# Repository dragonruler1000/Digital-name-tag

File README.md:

# Primortia nametag
i made this sense i wanted a way to have a name tag that had more personality then just a basic printed name tag. sense i have already designed a rp2040 devboard i decided to use that as the MCU. this has a pretty simple design so tobmake it your self you just need to get the pcb made then get all the other parts. sense one of the pins that is being used for the adc functionality in in a place that usually wouldn't have it printing my custom devboard is recommended unless you want to change the symbol to a regular pico.

BOM:
| Item Count | item name       | Unit price $ | Total Price* | Price with discounts* | Link                                                                                                               | Running total $* | Running total with coupons*    | part number | Notes                                   |
|------------|-----------------|--------------|--------------|-----------------------|--------------------------------------------------------------------------------------------------------------------|------------------|--------------------------------|-------------|-----------------------------------------|
| 1          | Blue LED        | 0.19         | 0.19         | 0.19                  | https://www.digikey.com/en/products/detail/american-bright-optoelectronics-corporation/BL-BBX1V4V-2-B02/22486905   | 0.2              | 0.2                            | 1           |                                         |
| 0          | Red LED         | 0            | 0            | 0                     | https://www.lcsc.com/product-detail/C99771.html                                                                    | 0.2              | 0.2                            | 2           | have some left over from a past project |
| 0          | Green LED       | 0            | 0            | 0                     | https://www.jameco.com/z/MCDL-5013GD-MCD-Electronics-LED-Green-Diffused-5mm-T-1-3-4-565nm-12-5mcd-60VA_693901.html | 0.2              | 0.2                            | 3           | have some left over from a past project |
| 1          | 5.1Ω resistor   | 0.1          | 0.1          | 0.1                   | https://www.digikey.com/en/products/detail/yageo/CFR-25JB-52-5R1/2238                                              | 0.31             | 0.31                           | 4           |                                         |
| 1          | 56Ω resistor    | 0.1          | 0.1          | 0.1                   | https://www.digikey.com/en/products/detail/te-connectivity-passive-product/LR1F56R/2381266                         | 0.42             | 0.42                           | 5           |                                         |
| 1          | 120Ω resistor   | 0.1          | 0.1          | 0.1                   | https://www.digikey.com/en/products/detail/ohmite/OK1215E-R52/5972032                                              | 0.53             | 0.53                           | 6           |                                         |
| 1          | 100kΩ resistor  | 0.1          | 0.1          | 0.1                   | https://www.digikey.com/en/products/detail/te-connectivity-passive-product/LR1F100K/2381157                        | 0.64             | 0.64                           | 7           |                                         |
| 1          | 68kΩ resistor   | 0.1          | 0.1          | 0.1                   | https://www.digikey.com/en/products/detail/yageo/MFR50SFTE52-68K/9151668                                           | 0.75             | 0.75                           | 8           |                                         |
| 1          | buzzer          | 0.76         | 0.76         | 0.76                  | https://www.digikey.com/en/products/detail/ole-wolff-electronics-inc/OWPB-1360P3-5-40-03/27621007                  | 1.56             | 1.56                           | 9           |                                         |
| 3          | buttons         | 0.13         | 0.39         | 0.39                  | https://www.digikey.com/en/products/detail/te-connectivity-alcoswitch-switches/1825910-6/1632536                   | 1.97             | 1.97                           | 10          | have one left over from a past project  |
| 1          | battery holder  | 2.29         | 2.29         | 2.29                  | https://www.digikey.com/en/products/detail/keystone-electronics/2479RB/2746483                                     | 4.4              | 4.4                            | 11          |                                         |
| 1          | 0.91” oled      | 5.02         | 5.02         | 5.02                  | https://www.lcsc.com/product-detail/C5248081.html                                                                  | 9.72             | 9.72                           | 12          |                                         |
| 1          | PCB             | 5.3          | 5.3          | 5.3                   | https://jlcpcb.com                                                                                                 | 15.34            | 15.34                          | 13          |                                         |
| 1          | JLCPCB shipping | 3.3          | 3.3          | 3.3                   |                                                                                                                    | 18.84            | 18.84                          | 14          |                                         |
| 1          | digikeyshipping | 6.99         | 6.99         | 6.99                  |                                                                                                                    | 26.25            | 26.25                          | 15          |                                         |
|            |                 |              |              |                       |                                                                                                                    |                  | *Rounded to two decimal places |             |                                         |

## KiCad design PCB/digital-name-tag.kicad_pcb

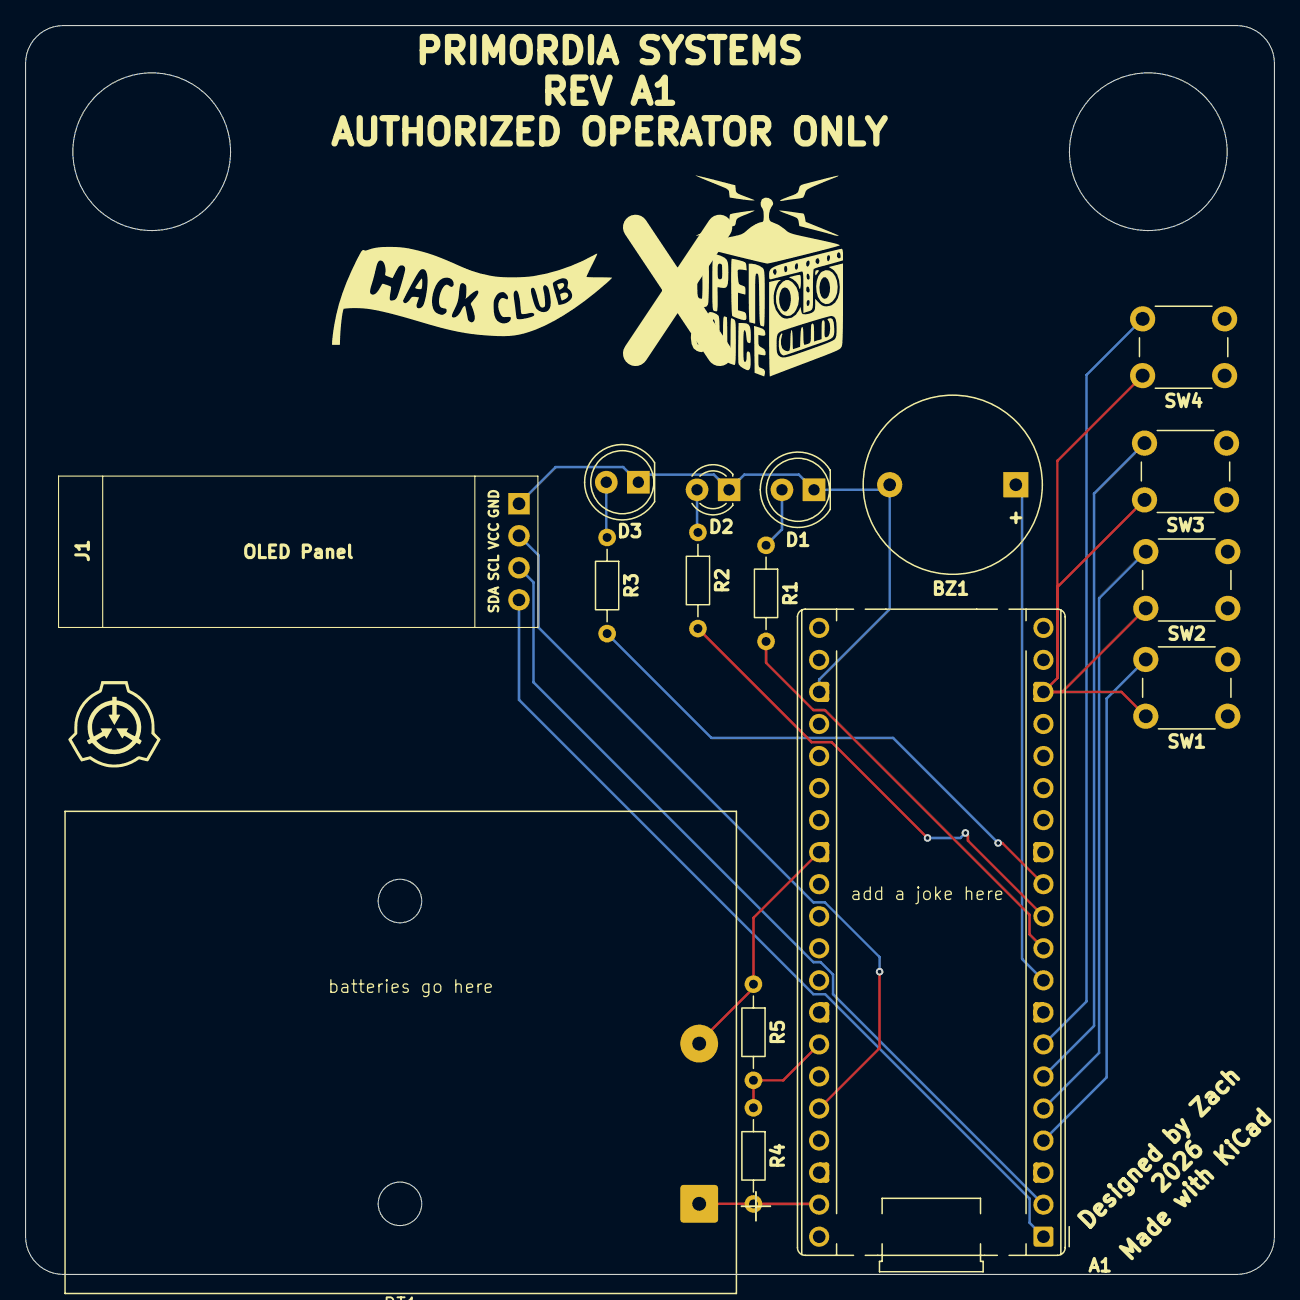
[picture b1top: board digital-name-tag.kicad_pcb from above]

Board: 2 copper layers, 99.0 x 99.0 mm, 16 parts (0 on the bottom side), 17 nets.

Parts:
A1: Primordia_Devboard; RaspberryPi_Pico_Common_THT
BT1: Battery; BatteryHolder_Keystone_2479_3xAAA
BZ1: Buzzer; Buzzer_D14mm_H7mm_P10mm
D1: BLUE; LED_D5.0mm
D2: RED; LED_D3.0mm
D3: GREEN; LED_D5.0mm
J1: Conn_01x04; SSD1306-0.91-OLED-4pin-128x32
R1: 5.1Ω; R_Axial_DIN0204_L3.6mm_D1.6mm_P7.62mm_Horizontal
R2: 56Ω; R_Axial_DIN0204_L3.6mm_D1.6mm_P7.62mm_Horizontal
R3: 120Ω; R_Axial_DIN0204_L3.6mm_D1.6mm_P7.62mm_Horizontal
R4: 100kΩ; R_Axial_DIN0204_L3.6mm_D1.6mm_P7.62mm_Horizontal
R5: 68kΩ; R_Axial_DIN0204_L3.6mm_D1.6mm_P7.62mm_Horizontal
SW1, SW2, SW3, SW4: SW_Push; SW_PUSH_6mm

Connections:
+3.3V: A1.36 (3V3), J1.2
GND: A1.3 (GND), A1.8 (GND), A1.13 (GND), A1.18 (GND), A1.23 (GND), A1.28 (GND), A1.38 (GND), BT1.2 (-), BZ1.2 (-), D1.1 (K), D2.1 (K), D3.1 (K), J1.1, R5.1, SW1.1, SW2.1, SW3.1, SW4.1
LED1: A1.10 (GPIO7), R1.2
LED2: A1.11 (GPIO8), R2.2
LED3: A1.12 (GPIO9), R3.2
unnamed: D1.2 (A), R1.1
unnamed: D2.2 (A), R2.1
unnamed: D3.2 (A), R3.1
SCL: A1.2 (GPIO1), J1.3
SDA: A1.1 (GPIO0), J1.4
VSYS: A1.39 (VSYS), BT1.1 (+), R4.2
batterylevel: A1.34 (GPIO26), R4.1, R5.2
button1: A1.4 (GPIO2), SW1.2
button2: A1.5 (GPIO3), SW2.2
button3: A1.6 (GPIO4), SW3.2
button4: A1.7 (GPIO5), SW4.2
buzzer: A1.9 (GPIO6), BZ1.1 (+)

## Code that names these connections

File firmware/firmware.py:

from machine import Pin, I2C, ADC
import ssd1306
import time

# --------------------
# Pin Configuration
# --------------------

SDA_PIN = 0
SCL_PIN = 1

BUTTON1_PIN = 2
BUTTON2_PIN = 3
BUTTON3_PIN = 4
BUTTON4_PIN = 5

BUZZER_PIN = 6

LED1_PIN = 7
LED2_PIN = 8
LED3_PIN = 9
LED4_PIN = 25

BATTERY_PIN = 26

# --------------------
# OLED Setup
# --------------------

i2c = I2C(
    0,
    scl=Pin(SCL_PIN),
    sda=Pin(SDA_PIN),
    freq=400000
)

oled = ssd1306.SSD1306_I2C(
    128,
    32,
    i2c
)

# --------------------
# Button Setup
# --------------------

buttons = [
    Pin(BUTTON1_PIN, Pin.IN, Pin.PULL_UP),
    Pin(BUTTON2_PIN, Pin.IN, Pin.PULL_UP),
    Pin(BUTTON3_PIN, Pin.IN, Pin.PULL_UP),
    Pin(BUTTON4_PIN, Pin.IN, Pin.PULL_UP),
]

last_states = [1, 1, 1, 1]

# --------------------
# LED Setup
# --------------------

led1 = Pin(LED1_PIN, Pin.OUT)
led2 = Pin(LED2_PIN, Pin.OUT)
led3 = Pin(LED3_PIN, Pin.OUT)
led4 = Pin(LED4_PIN, Pin.OUT)

# --------------------
# Battery Setup
# --------------------

battery_adc = ADC(BATTERY_PIN)

LOW_BATTERY_THRESHOLD = 30

# --------------------
# Pages
# --------------------

page = 0

# --------------------
# Battery Functions
# --------------------

def get_battery_voltage():
    """
    Read battery voltage.
    Assumes 100k/100k voltage divider.
    """

    raw = battery_adc.read_u16()

    # Convert ADC reading to voltage
    voltage = (raw / 65535) * 3.3

    # Undo divider (x2)
    battery_voltage = voltage * 2

    return battery_voltage


def get_battery_percent():
    """
    Approximate percentage for 3x AAA alkaline batteries.

    4.5V = full
    3.3V = empty
    """

    voltage = get_battery_voltage()

    percent = int(((voltage - 3.3) / (4.5 - 3.3)) * 100)

    # Clamp range
    percent = max(0, min(100, percent))

    return percent

# --------------------
# Display Functions
# --------------------

def draw_page():
    oled.fill(0)

    battery = get_battery_percent()

    if page == 0:
        oled.text("Zach", 0, 0)
        oled.text("Indie Dev", 0, 12)
        oled.text("RP2040 Badge", 0, 24)

    elif page == 1:
        oled.text("Primordia", 0, 0)
        oled.text("Systems", 0, 12)
        oled.text("STATUS: OK", 0, 24)

    elif page == 2:
        oled.text("Battery", 0, 0)
        oled.text(str(battery) + "%", 0, 12)

        voltage = round(get_battery_voltage(), 2)
        oled.text(str(voltage) + "V", 0, 24)

    oled.show()

# --------------------
# Button Actions
# --------------------

def handle_button_press(index):
    global page

    # Button 1
    if index == 0:
        page = (page + 1) % 3
        draw_page()

    # Button 2
    elif index == 1:
        led1.toggle()

    # Button 3
    elif index == 2:
        led3.toggle()

    # Button 4
    elif index == 3:
        led4.toggle()

# --------------------
# Initial Draw
# --------------------

draw_page()

# --------------------
# Main Loop
# --------------------

while True:

    # Check Buttons
    for i in range(4):

        current = buttons[i].value()

        # Detect press
        if last_states[i] == 1 and current == 0:
            handle_button_press(i)

        last_states[i] = current

    # Battery Warning LED
    battery_percent = get_battery_percent()

    if battery_percent < LOW_BATTERY_THRESHOLD:
        led2.on()
    else:
        led2.off()

    time.sleep(0.05)

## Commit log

2026-05-18 Create .gitignore for KiCad project
    Add .gitignore for KiCad project files and temporary files
2026-05-18 did a good chunk of work
2026-05-18 layed out the pcb and added silkscreen art
2026-05-18 tjere where some changes not sure what
2026-05-19 worked on bom and started on firmware
2026-05-20 added csv version for the BOM
2026-05-20 Add BOM table to README
    Added BOM table with item details and links.
2026-05-22 added a image of the 3d model and updated battery holder footprint to be a 3xAAA holder
2026-05-22 this might work
2026-05-22 added more silkscreen art
2026-05-25 updated gerbers
2026-06-03 Update image in README and BOM section
    Replaced 3d-model-back.png with image.png in README.
